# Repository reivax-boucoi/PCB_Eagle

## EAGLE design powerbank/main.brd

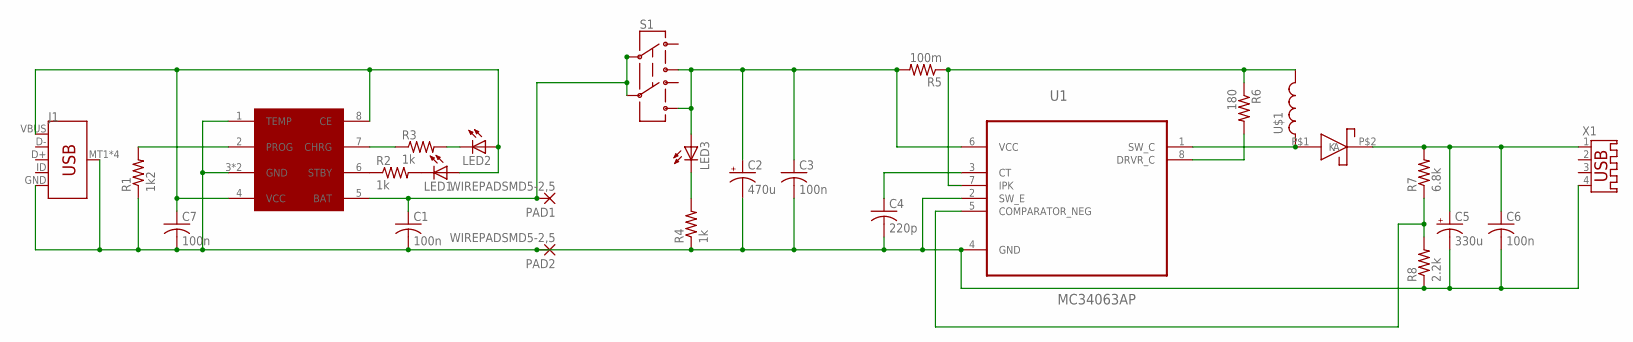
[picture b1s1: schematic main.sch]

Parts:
C1, C3, C6, C7: 100n; C0603
C2: 470u; E5-10,5
C4: 220p; C025-025X050
C5: 330u; E3,5-8
CH1: TP4056; SOP8
D1: SS34; DO-214AB
J1: USB_MICRO-B_SMT; USB-MICROB
LED1, LED2, LED3: LEDCHIP-LED0805; CHIP-LED0805
PAD1, PAD2: WIREPADSMD5-2,5; 5-2,5
R1: 1k2; M0805
R2, R3, R4: 1k; M0805
R5: 100m; R0603
R6: 180; 0309V
R7: 6.8k; 0204/5
R8: 2.2k; M0805
S1: SWITCH-DPDTEG2211; EG2211
U1: MC34063AP; DIP254P762X508-8
U$1: DO540H
X1: USB-A003

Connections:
GND: C1.2, C2.-, C3.2, C4.2, C5.-, C6.2, C7.2, CH1.1 (TEMP), CH1.3 (GND), CH1.9 (GND), J1.GND, J1.MT1 (SHIELD), J1.MT2 (SHIELD), J1.P$1 (SHIELD), J1.P$2 (SHIELD), PAD2.1, R1.1, R4.1, R8.1, U1.2 (SW_E), U1.4 (GND), X1.4
unnamed: CH1.6 (STBY), R2.1
unnamed: C1.1, CH1.5 (BAT), PAD1.1, S1.P1 (2), S1.P2 (5)
unnamed: CH1.7 (CHRG), R3.1
unnamed: D1.P$1 (A), U1.1 (SW_C), U$1.P$2
unnamed: LED1.C, R2.2
unnamed: LED2.C, R3.2
unnamed: C7.1, CH1.4 (VCC), CH1.8 (CE), J1.VBUS, LED1.A, LED2.A
unnamed: LED3.C, R4.2
unnamed: CH1.2 (PROG), R1.2
unnamed: C2.+, C3.1, LED3.A, R5.2, S1.P1-TB (3), S1.P2-TB (6), U1.6 (VCC)
unnamed: C5.+, C6.1, D1.P$2 (K), R7.2, X1.1
unnamed: R7.1, R8.2, U1.5 (COMPARATOR_NEG)
unnamed: R6.2, U1.8 (DRVR_C)
unnamed: C4.1, U1.3 (CT)
unnamed: R5.1, R6.1, U1.7 (IPK), U$1.P$1

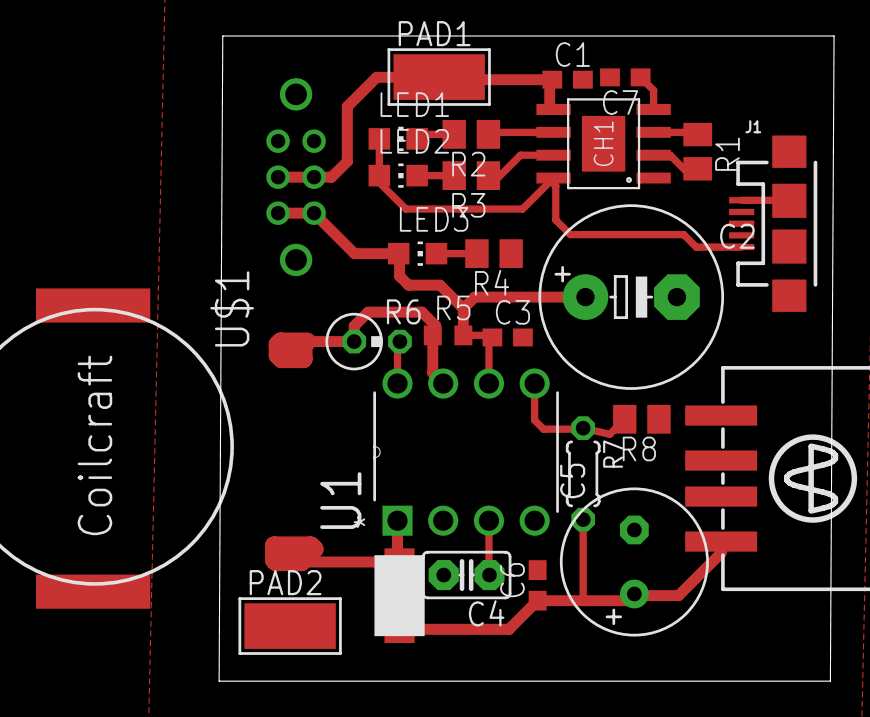
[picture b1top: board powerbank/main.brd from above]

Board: 2 copper layers, 34.2 x 35.8 mm, 27 parts (0 on the bottom side), 16 nets.

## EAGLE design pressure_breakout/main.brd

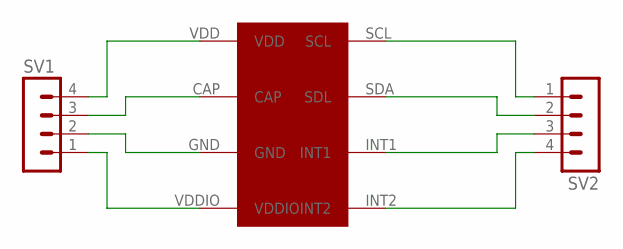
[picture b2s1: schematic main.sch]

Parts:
SV1, SV2: MA04-1
U$1: MPL3115A2; LGA8_CAN

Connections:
unnamed: SV1.4, U$1.VDD
unnamed: SV1.3, U$1.CAP
unnamed: SV1.2, U$1.GND
unnamed: SV1.1, U$1.VDDIO
unnamed: SV2.4, U$1.INT2
unnamed: SV2.3, U$1.INT1
unnamed: SV2.2, U$1.SDA (SDL)
unnamed: SV2.1, U$1.SCL

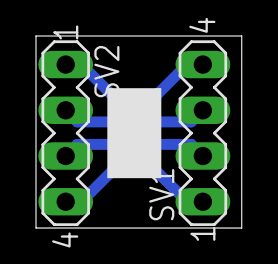
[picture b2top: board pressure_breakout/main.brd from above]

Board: 2 copper layers, 11.4 x 10.7 mm, 3 parts (0 on the bottom side), 8 nets.

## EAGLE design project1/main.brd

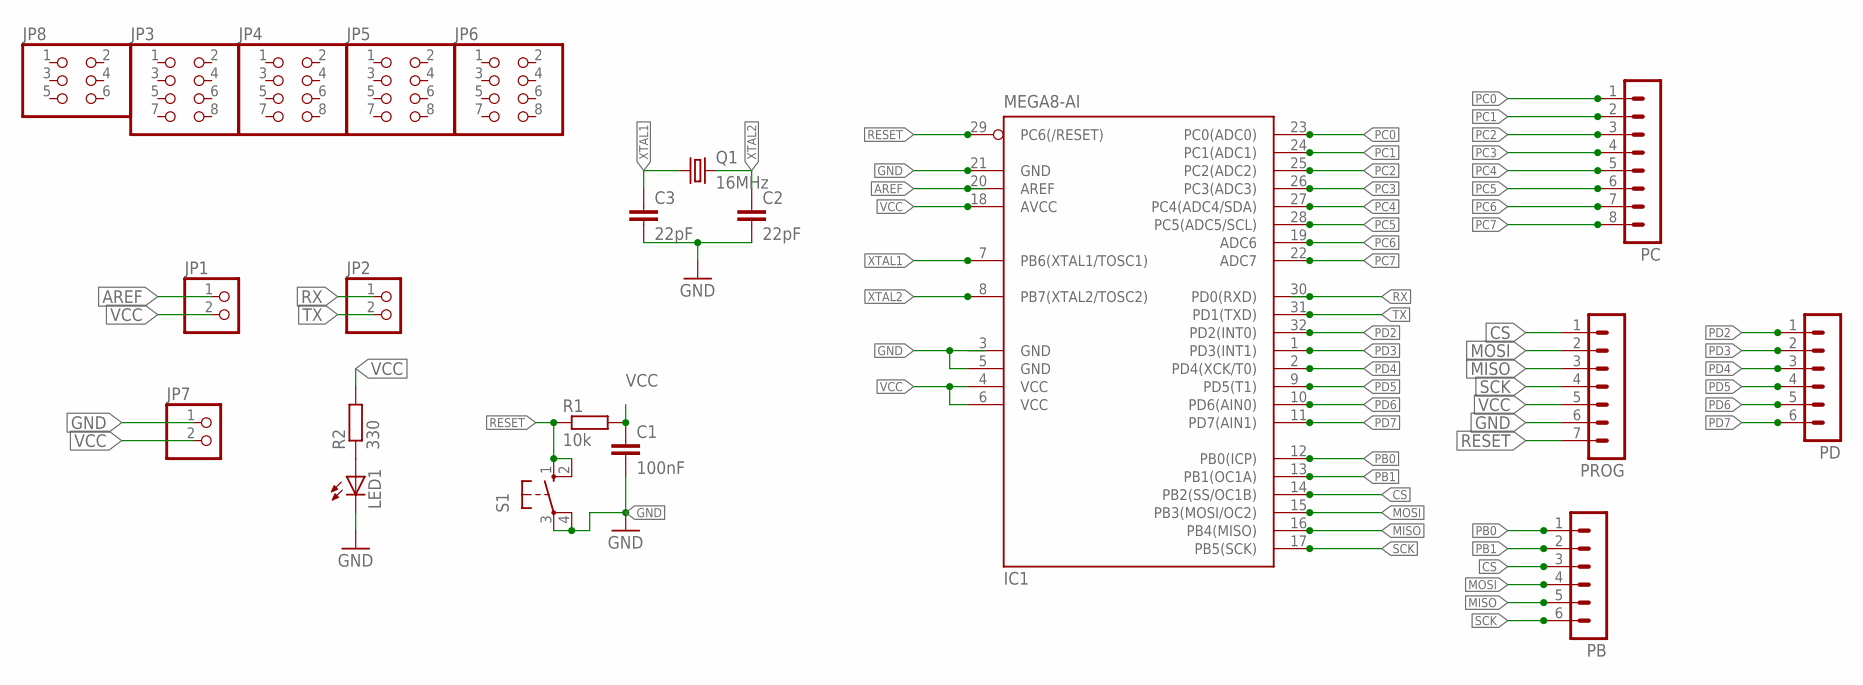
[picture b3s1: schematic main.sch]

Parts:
C1: 100nF; C025-025X050
C2, C3: 22pF; C025-025X050
IC1: MEGA8-AI; TQFP32-08
JP1, JP2, JP7: PINHD-1X2; 1X02
JP3, JP4, JP5, JP6: PINHD-2X4; 2X04
JP8: PINHD-2X3; 2X03
LED1: LED3MM
PB: MA06-1
PC: MA08-1
PD: MA06-1
PROG: MA07-1
Q1: 16MHz; HC49/S
R1: 10k; 0207/12
R2: 330; M0805
S1: 10-XX; B3F-10XX

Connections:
AREF: IC1.20 (AREF), JP1.1
CS: IC1.14 (PB2(SS/OC1B)), PB.3, PROG.1
GND: C1.2, C2.2, C3.2, IC1.3 (GND), IC1.5 (GND), IC1.21 (GND), JP7.1, LED1.K (C), PROG.6, S1.3, S1.4 (P1)
MISO: IC1.16 (PB4(MISO)), PB.5, PROG.3
MOSI: IC1.15 (PB3(MOSI/OC2)), PB.4, PROG.2
unnamed: LED1.A, R2.1
PB0: IC1.12 (PB0(ICP)), PB.1
PB1: IC1.13 (PB1(OC1A)), PB.2
PC0: IC1.23 (PC0(ADC0)), PC.1
PC1: IC1.24 (PC1(ADC1)), PC.2
PC2: IC1.25 (PC2(ADC2)), PC.3
PC3: IC1.26 (PC3(ADC3)), PC.4
PC4: IC1.27 (PC4(ADC4/SDA)), PC.5
PC5: IC1.28 (PC5(ADC5/SCL)), PC.6
PC6: IC1.19 (ADC6), PC.7
PC7: IC1.22 (ADC7), PC.8
PD2: IC1.32 (PD2(INT0)), PD.1
PD3: IC1.1 (PD3(INT1)), PD.2
PD4: IC1.2 (PD4(XCK/T0)), PD.3
PD5: IC1.9 (PD5(T1)), PD.4
PD6: IC1.10 (PD6(AIN0)), PD.5
PD7: IC1.11 (PD7(AIN1)), PD.6
RESET: IC1.29 (PC6(/RESET)), PROG.7, R1.1, S1.1 (S), S1.2 (S1)
RX: IC1.30 (PD0(RXD)), JP2.1
SCK: IC1.17 (PB5(SCK)), PB.6, PROG.4
TX: IC1.31 (PD1(TXD)), JP2.2
VCC: C1.1, IC1.4 (VCC), IC1.6 (VCC), IC1.18 (AVCC), JP1.2, JP7.2, PROG.5, R1.2, R2.2
XTAL1: C3.1, IC1.7 (PB6(XTAL1/TOSC1)), Q1.1
XTAL2: C2.1, IC1.8 (PB7(XTAL2/TOSC2)), Q1.2

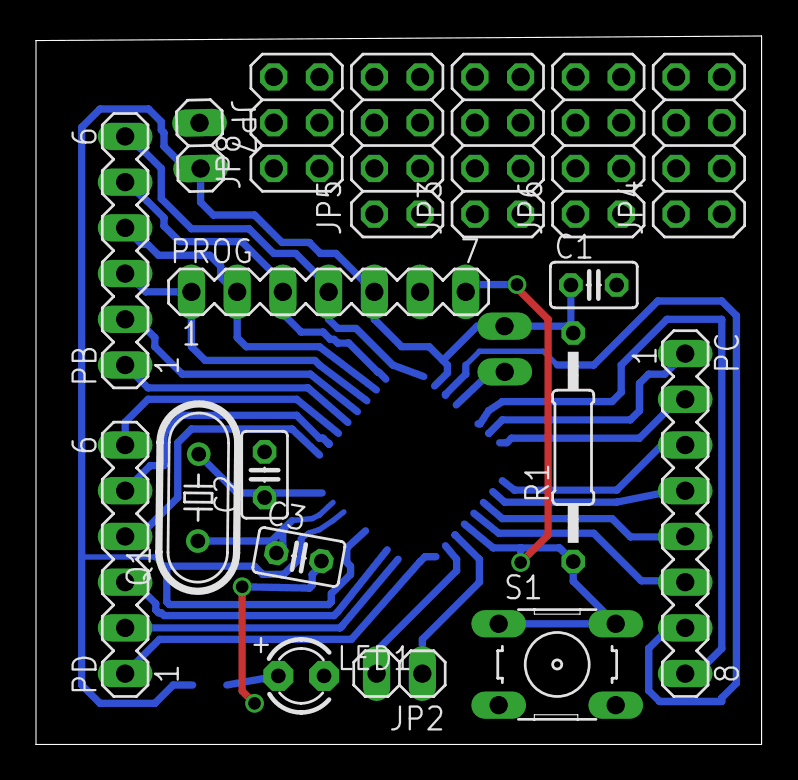
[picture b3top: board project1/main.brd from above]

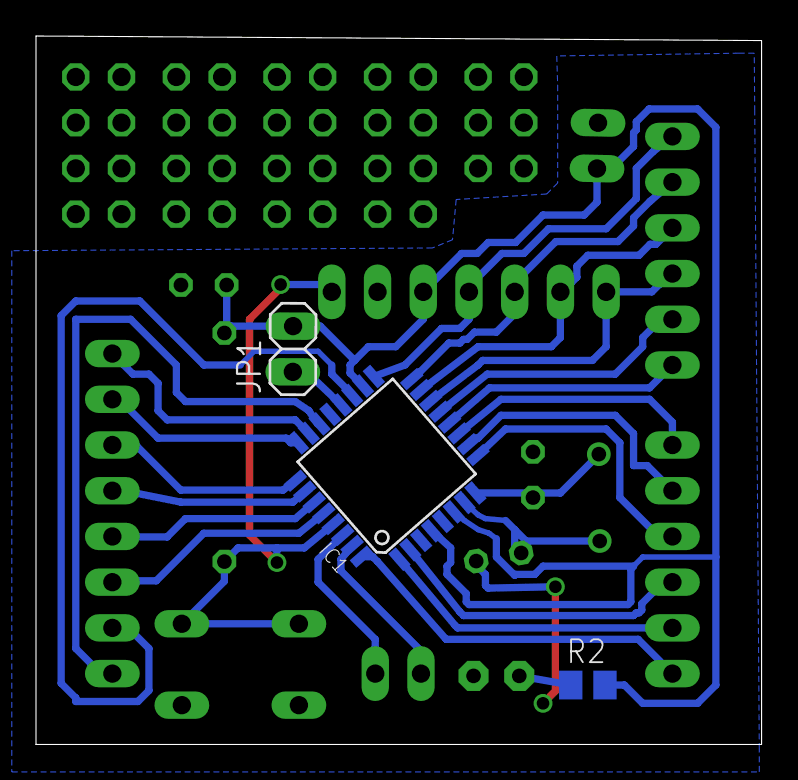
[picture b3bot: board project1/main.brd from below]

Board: 2 copper layers, 40.3 x 39.4 mm, 21 parts (3 on the bottom side), 29 nets.

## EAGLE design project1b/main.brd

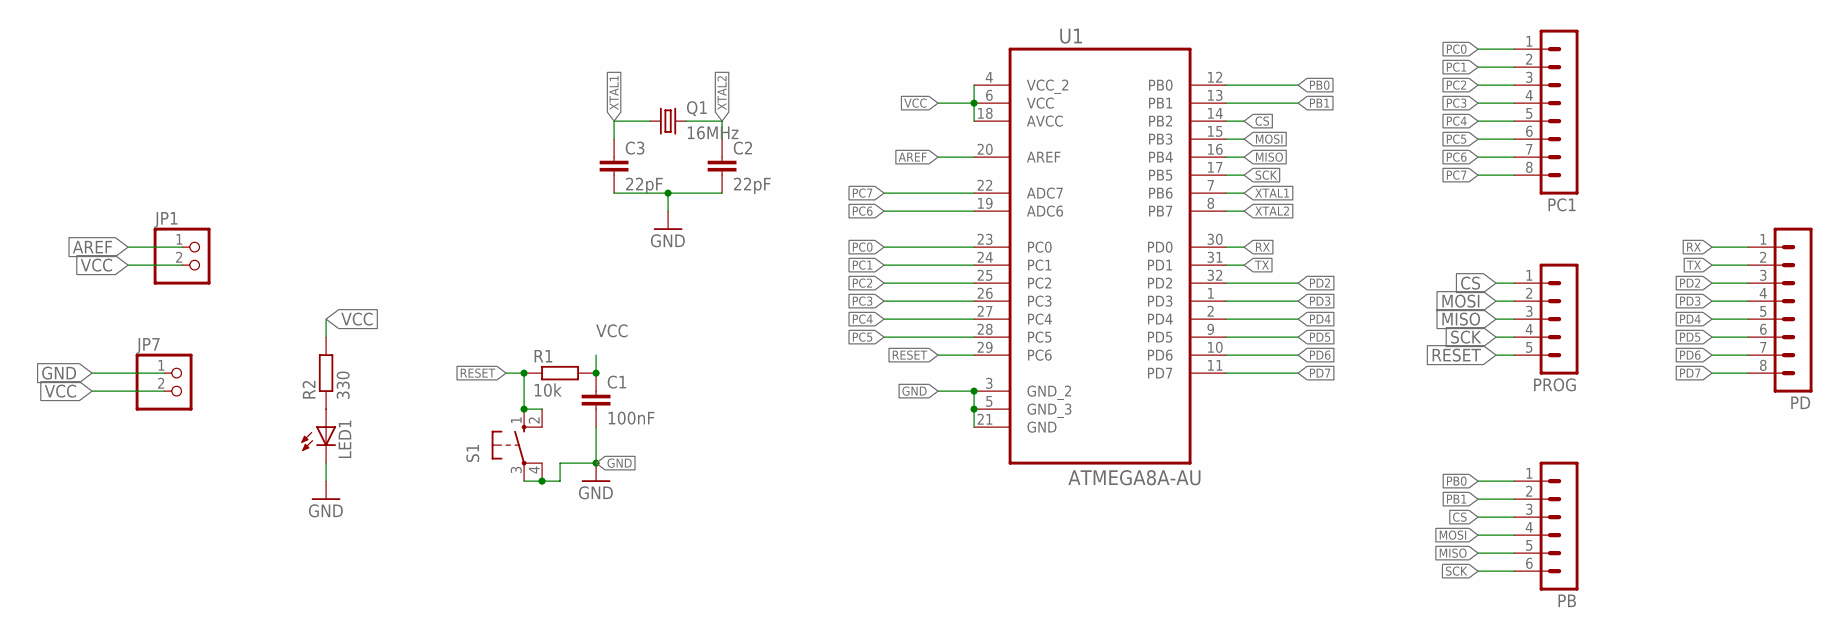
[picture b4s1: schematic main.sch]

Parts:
C1: 100nF; C025-025X050
C2, C3: 22pF; C025-025X050
JP1, JP7: PINHD-1X2; 1X02
LED1: LED3MM
PB: MA06-1
PC1: MA08-1
PD: MA08-1
PROG: MA05-1
Q1: 16MHz; HC49/S
R1: 10k; M0805
R2: 330; M0805
S1: 10-XX; B3F-10XX
U1: ATMEGA8A-AU; QFP80P900X900X120-32N

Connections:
AREF: JP1.1, U1.20 (AREF)
CS: PB.3, PROG.1, U1.14 (PB2)
GND: C1.2, C2.2, C3.2, JP7.1, LED1.K (C), S1.3, S1.4 (P1), U1.3 (GND_2), U1.5 (GND_3), U1.21 (GND)
MISO: PB.5, PROG.3, U1.16 (PB4)
MOSI: PB.4, PROG.2, U1.15 (PB3)
unnamed: LED1.A, R2.1
PB0: PB.1, U1.12 (PB0)
PB1: PB.2, U1.13 (PB1)
PC0: PC1.1, U1.23 (PC0)
PC1: PC1.2, U1.24 (PC1)
PC2: PC1.3, U1.25 (PC2)
PC3: PC1.4, U1.26 (PC3)
PC4: PC1.5, U1.27 (PC4)
PC5: PC1.6, U1.28 (PC5)
PC6: PC1.7, U1.19 (ADC6)
PC7: PC1.8, U1.22 (ADC7)
PD2: PD.3, U1.32 (PD2)
PD3: PD.4, U1.1 (PD3)
PD4: PD.5, U1.2 (PD4)
PD5: PD.6, U1.9 (PD5)
PD6: PD.7, U1.10 (PD6)
PD7: PD.8, U1.11 (PD7)
RESET: PROG.5, R1.1, S1.1 (S), S1.2 (S1), U1.29 (PC6)
RX: PD.1, U1.30 (PD0)
SCK: PB.6, PROG.4, U1.17 (PB5)
TX: PD.2, U1.31 (PD1)
VCC: C1.1, JP1.2, JP7.2, R1.2, R2.2, U1.4 (VCC_2), U1.6 (VCC), U1.18 (AVCC)
XTAL1: C3.1, Q1.1, U1.7 (PB6)
XTAL2: C2.1, Q1.2, U1.8 (PB7)

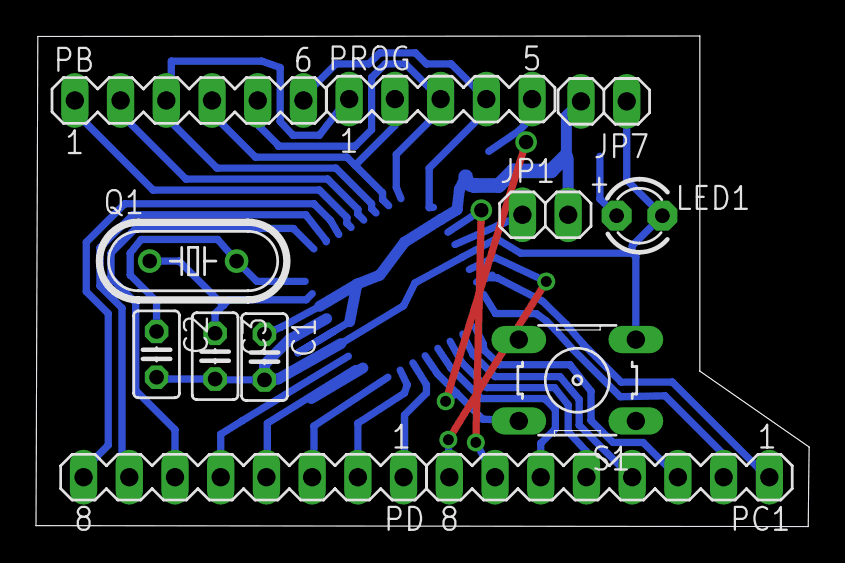
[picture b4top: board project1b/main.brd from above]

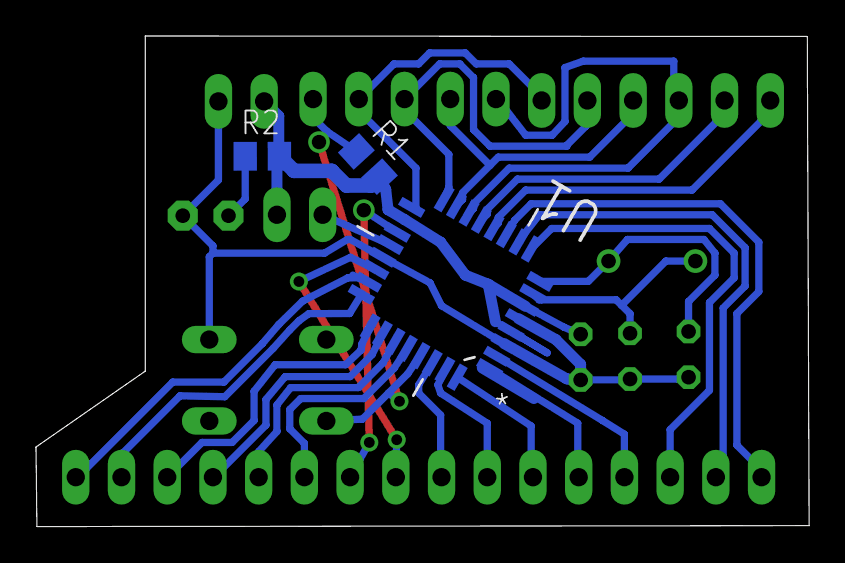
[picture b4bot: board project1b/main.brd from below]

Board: 2 copper layers, 43.0 x 27.3 mm, 15 parts (3 on the bottom side), 29 nets.

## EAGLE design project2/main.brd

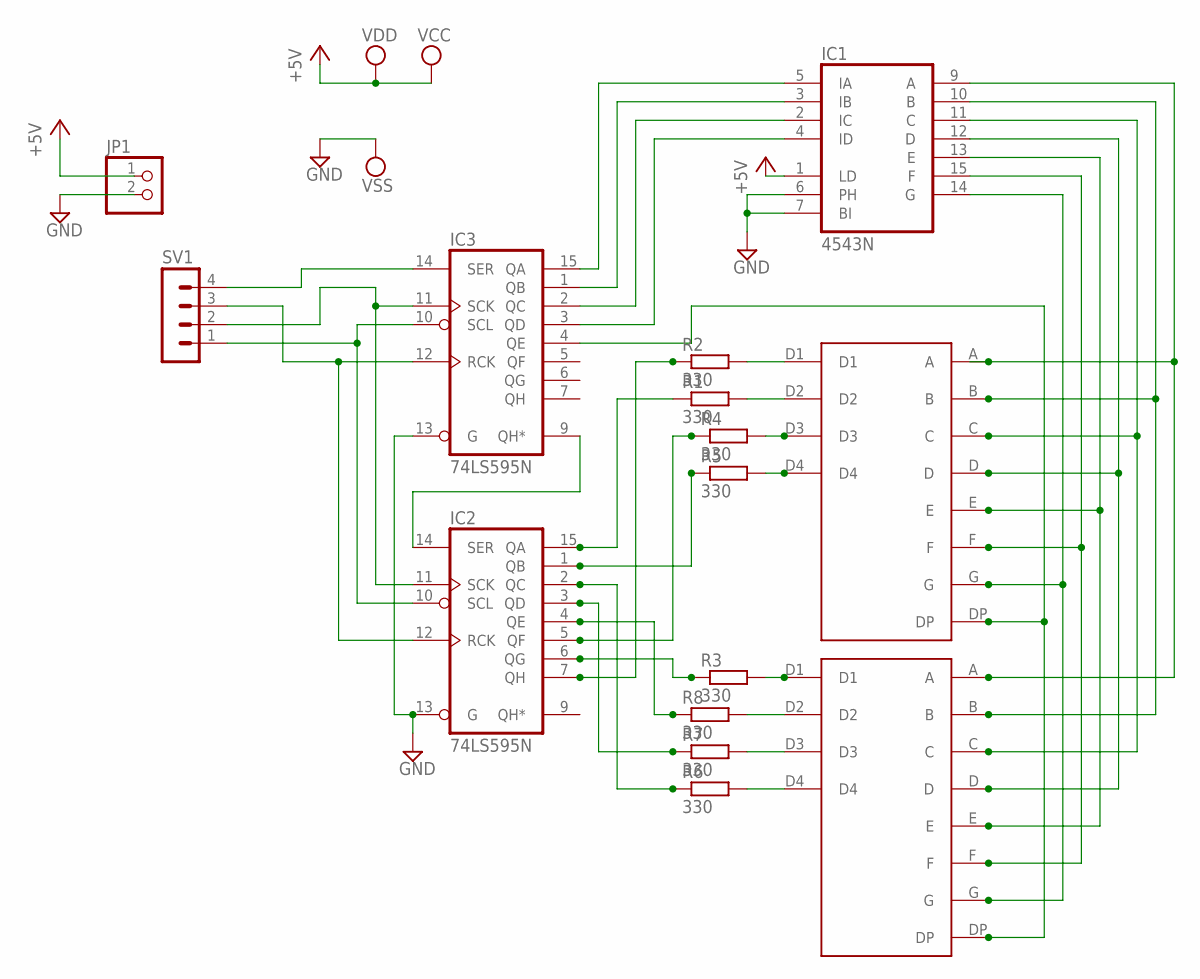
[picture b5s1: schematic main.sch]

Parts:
IC1: 4543N; DIL16
IC2, IC3: 74LS595N; DIL16
JP1: PINHD-1X2; 1X02
R1: 330; P0817/22
R2, R3, R4, R5, R6, R7, R8: 330; R0805
SV1: MA04-1
U$1, U$2: 4-DIGIT_7-SEGMENT-DISPLAYTHROUGH-HOLE; 4-DIGIT_7-SEGMENT-DISPLAY

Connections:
+5V: IC1.1 (LD), IC1.16 (VDD), IC2.16 (VCC), IC3.16 (VCC), JP1.1
GND: IC1.6 (PH), IC1.7 (BI), IC1.8 (VSS), IC2.8 (GND), IC2.13 (G), IC3.8 (GND), IC3.13 (G), JP1.2
unnamed: IC1.9 (A), U$1.A, U$2.A
unnamed: IC1.10 (B), U$1.B, U$2.B
unnamed: IC1.11 (C), U$1.C, U$2.C
unnamed: IC1.12 (D), U$1.D, U$2.D
unnamed: IC1.13 (E), U$1.E, U$2.E
unnamed: IC1.15 (F), U$1.F, U$2.F
unnamed: IC1.14 (G), U$1.G, U$2.G
unnamed: IC3.4 (QE), U$1.DP, U$2.DP
unnamed: R2.2, U$1.D1
unnamed: R1.2, U$1.D2
unnamed: R3.2, U$2.D1
unnamed: R5.2, U$1.D4
unnamed: R4.2, U$1.D3
unnamed: R8.2, U$2.D2
unnamed: R7.2, U$2.D3
unnamed: R6.2, U$2.D4
unnamed: IC2.14 (SER), IC3.9 (QH*)
unnamed: IC2.12 (RCK), IC3.12 (RCK), SV1.3
unnamed: IC2.10 (SCL), IC3.10 (SCL), SV1.1
unnamed: IC2.11 (SCK), IC3.11 (SCK), SV1.2
unnamed: IC2.15 (QA), R1.1
unnamed: IC2.7 (QH), R2.1
unnamed: IC2.6 (QG), R3.1
unnamed: IC2.5 (QF), R4.1
unnamed: IC2.1 (QB), R5.1
unnamed: IC2.2 (QC), R6.1
unnamed: IC2.3 (QD), R7.1
unnamed: IC2.4 (QE), R8.1
unnamed: IC3.14 (SER), SV1.4
unnamed: IC1.5 (IA), IC3.15 (QA)
unnamed: IC1.3 (IB), IC3.1 (QB)
unnamed: IC1.2 (IC), IC3.2 (QC)
unnamed: IC1.4 (ID), IC3.3 (QD)

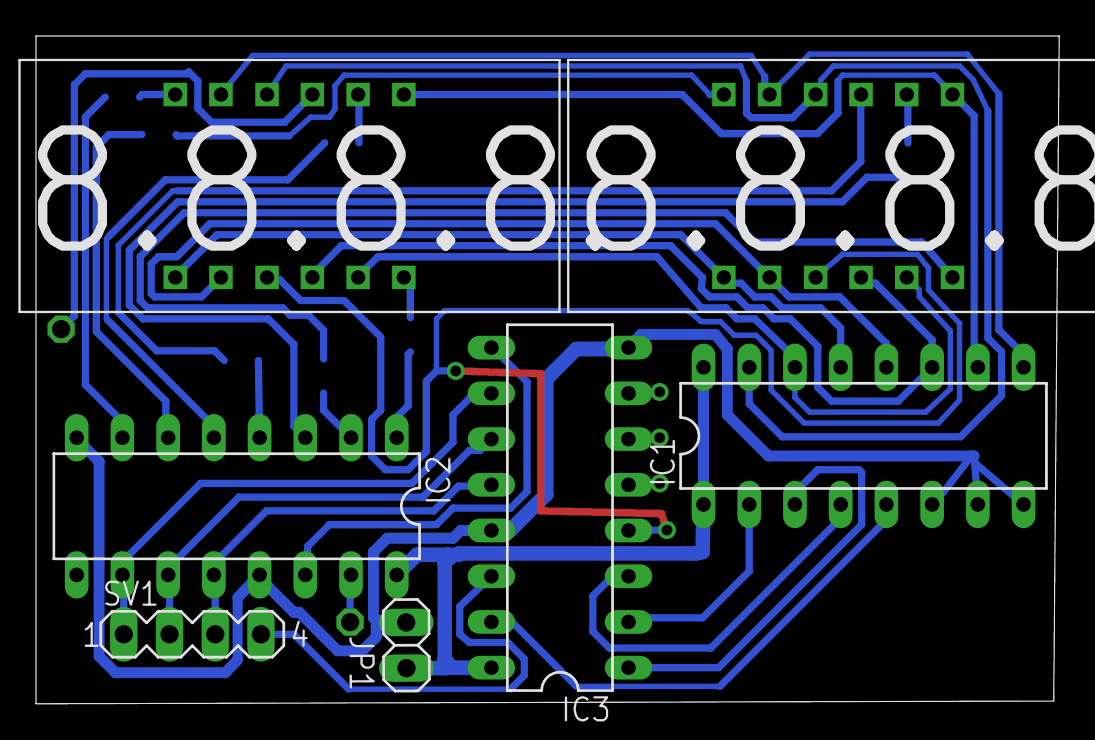
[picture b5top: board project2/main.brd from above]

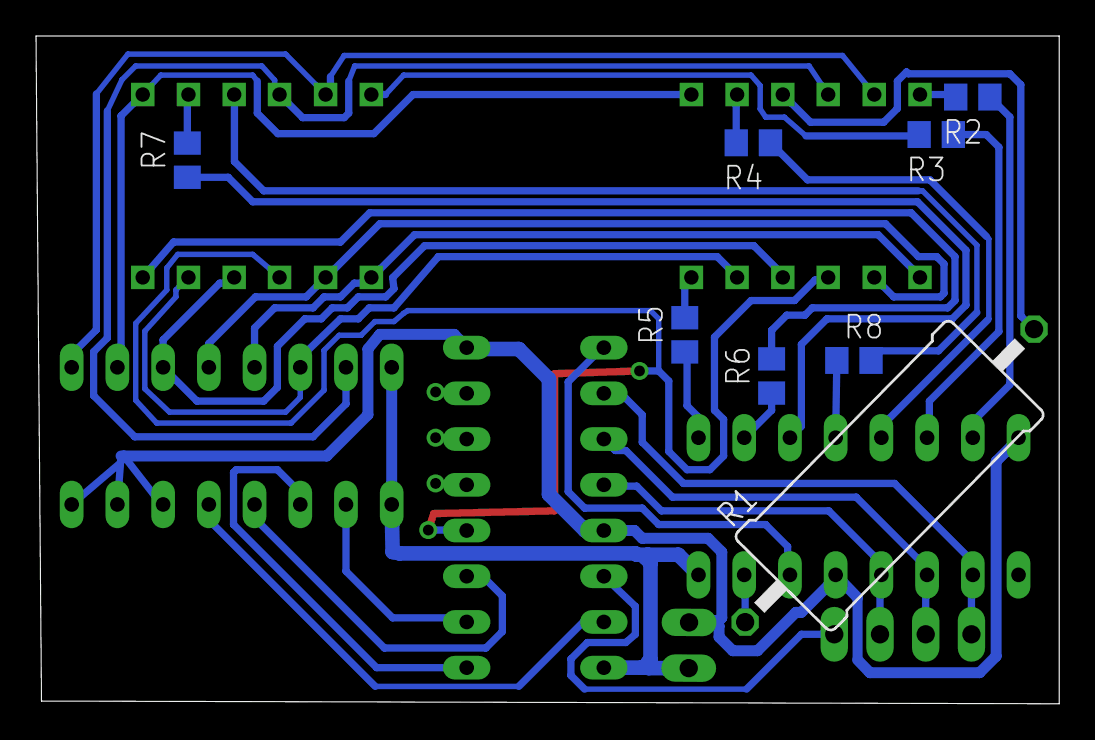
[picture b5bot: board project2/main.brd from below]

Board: 2 copper layers, 56.8 x 37.1 mm, 15 parts (8 on the bottom side), 35 nets.

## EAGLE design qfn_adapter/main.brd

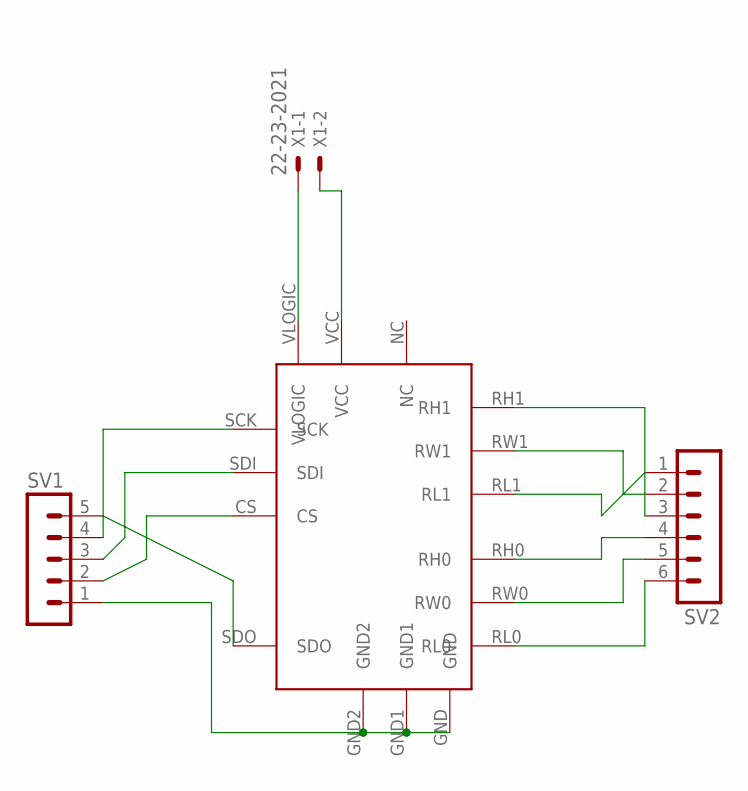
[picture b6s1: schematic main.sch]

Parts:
SV1: MA05-1
SV2: MA06-1
U$1: ISL23428; UTQFN16
X1: 22-23-2021

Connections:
unnamed: SV1.1, U$1.GND, U$1.GND1, U$1.GND2
unnamed: SV1.4, U$1.SCK
unnamed: SV1.3, U$1.SDI
unnamed: SV1.2, U$1.CS
unnamed: SV1.5, U$1.SDO
unnamed: SV2.6, U$1.RL0
unnamed: SV2.5, U$1.RW0
unnamed: SV2.4, U$1.RH0
unnamed: SV2.3, U$1.RH1
unnamed: SV2.2, U$1.RW1
unnamed: SV2.1, U$1.RL1
unnamed: U$1.VLOGIC, X1.1
unnamed: U$1.VCC, X1.2

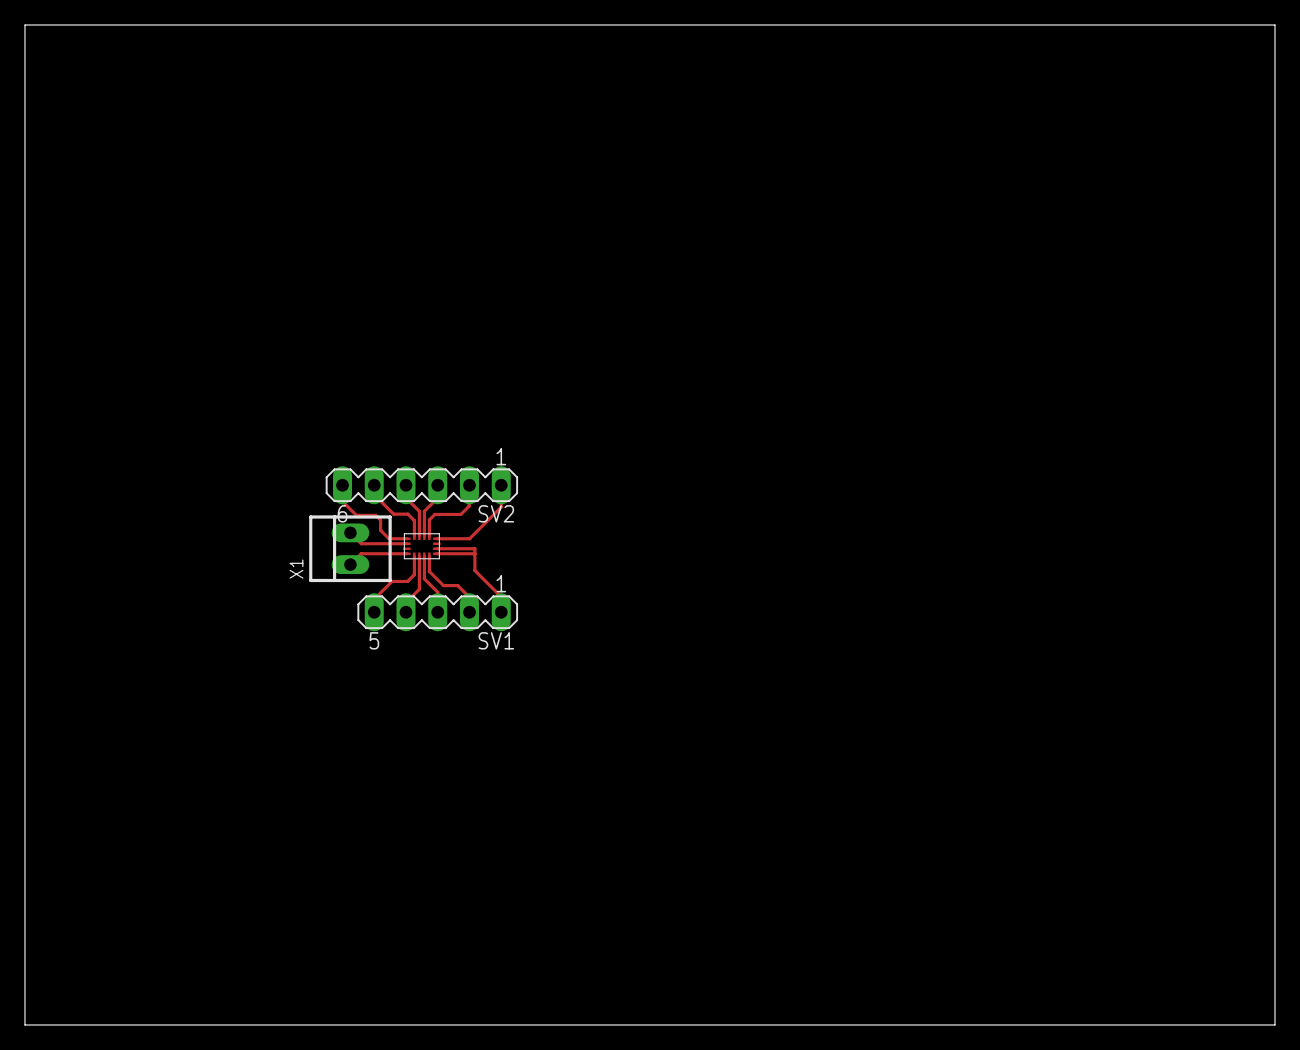
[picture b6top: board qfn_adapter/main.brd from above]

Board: 2 copper layers, 100.0 x 80.0 mm, 4 parts (0 on the bottom side), 13 nets.

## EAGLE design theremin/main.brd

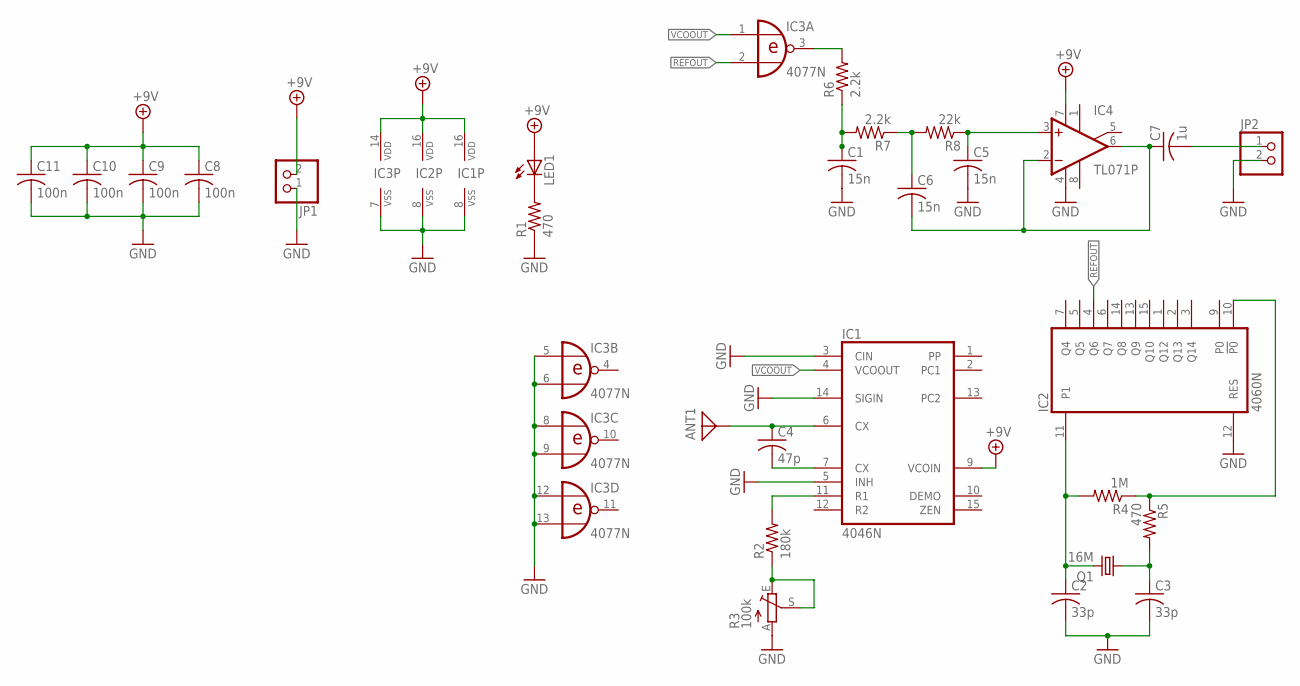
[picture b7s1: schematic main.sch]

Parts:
ANT1: ANTENNA; PAD-01
C1, C5, C6: 15n; C050-025X075
C2, C3: 33p; C050-025X075
C4: 47p; C050-025X075
C7: 1u; C050-025X075
C8, C9, C10, C11: 100n; C050-025X075
IC1: 4046N; DIL16
IC2: 4060N; DIL16
IC3: 4077N; DIL14
IC4: TL071P; DIL08
JP1, JP2: PINHD-1X2; 1X02
LED1: LED3MM
Q1: 16M; HC49/S
R1, R5: 470; 0204/7
R2: 180k; 0207/10
R3: 100k; RJ9W
R4: 1M; 0204/7
R6, R7: 2.2k; 0204/7
R8: 22k; 0204/7

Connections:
+9V: C8.1, C9.1, C10.1, C11.1, IC1.9 (VCOIN), IC1.16 (VDD), IC2.16 (VDD), IC3.14 (VDD), IC4.7 (V+), JP1.2, LED1.A
GND: C1.2, C2.2, C3.2, C5.2, C8.2, C9.2, C10.2, C11.2, IC1.3 (CIN), IC1.5 (INH), IC1.8 (VSS), IC1.14 (SIGIN), IC2.8 (VSS), IC2.12 (RES), IC3.5 (I0), IC3.6 (I1), IC3.7 (VSS), IC3.8 (I0), IC3.9 (I1), IC3.12 (I0), IC3.13 (I1), IC4.4 (V-), JP1.1, JP2.2, R1.1, R3.A
unnamed: IC2.10 (!P0), R4.1, R5.1
unnamed: LED1.K (C), R1.2
unnamed: C2.1, IC2.11 (P1), Q1.2, R4.2
unnamed: C3.1, Q1.1, R5.2
unnamed: C6.1, R7.1, R8.2
unnamed: IC1.11 (R1), R2.2
unnamed: R2.1, R3.E, R3.S
unnamed: C4.2, IC1.7 (CX)
unnamed: ANT1.1, C4.1, IC1.6 (CX)
unnamed: C1.1, R6.1, R7.2
unnamed: IC3.3 (O), R6.2
unnamed: C5.1, IC4.3 (+IN), R8.1
unnamed: C6.2, C7.1, IC4.2 (-IN), IC4.6 (OUT)
unnamed: C7.2, JP2.1
REFOUT: IC2.4 (Q6), IC3.2 (I1)
VCOOUT: IC1.4 (VCOOUT), IC3.1 (I0)

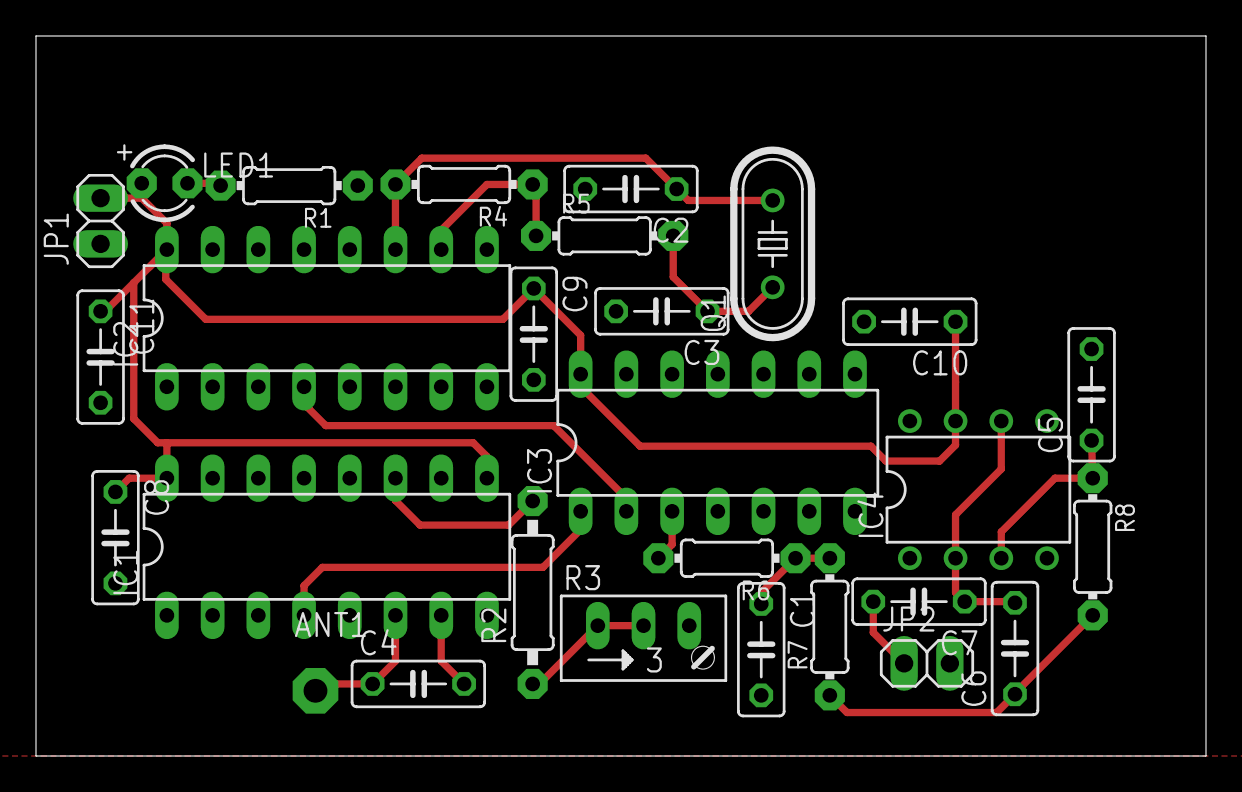
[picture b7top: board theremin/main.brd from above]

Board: 2 copper layers, 65.0 x 40.0 mm, 28 parts (0 on the bottom side), 18 nets.

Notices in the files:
parts and their libraries:
SparkFun-Connectors: Licensing: Creative Commons ShareAlike 4.0 International - https://creativecommons.org/licenses/by-sa/4.0
